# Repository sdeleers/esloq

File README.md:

# esloq
Project date: 2014-2016

Esloq is a startup I worked on from 2014 to 2016. All code written by Kenny Kuchera and me.

Esloq is a door lock that can be opened with a smartphone via Bluetooth. It consists of a wooden box that is mounted on the door lock cylinder. The wooden box contains the printed circuit board and a motor that actuates the lock.

A demo video of the esloq:

Esloq uses authentication and encryption to ensure that only the people you invite can enter. Whenever you want to open a door with your phone, the phone requests a ticket from the esloq webserver. The server returns the ticket that is authenticated encrypted under a symmetric key that is shared between the door lock and the esloq webserver (the phone does not have this key). The phone then forwards this ticket to the lock which verifies its authenticity and opens the door if it's valid.

This repository contains:
- the Kicad design files to make the printed circuit board (folder /pcb/)
- the software running on the microcontroller (folder /firmware/)
- the Android app that connects with the door lock (folder /android/)
- the code running on the webserver (folder /webserver/)

The printed circuit board:

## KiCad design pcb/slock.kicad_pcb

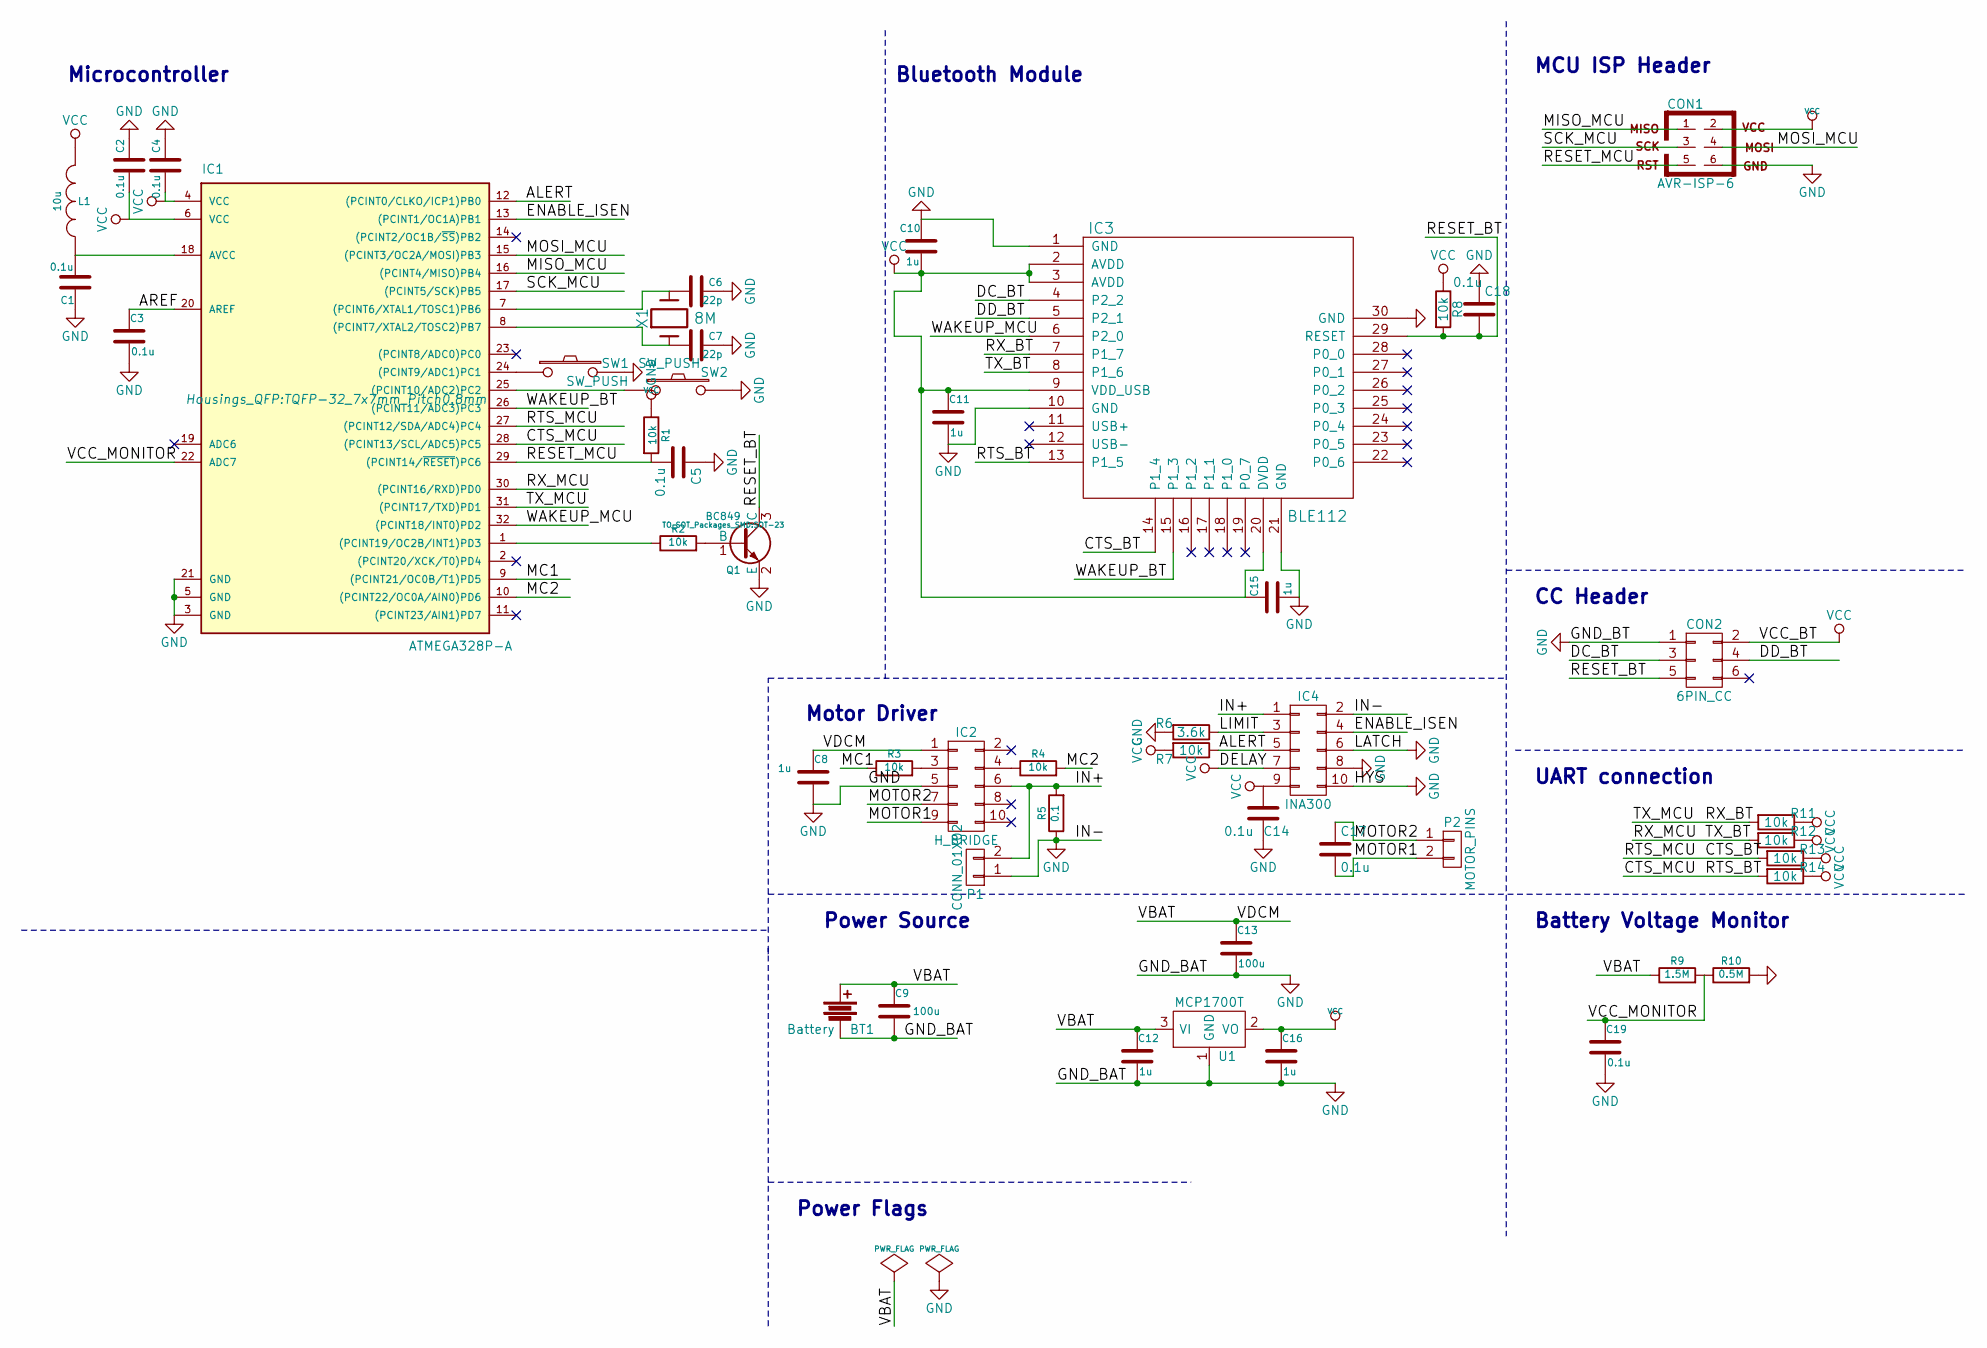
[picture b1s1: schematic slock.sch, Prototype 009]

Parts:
BT1: Battery; Connectors_JST_S2B-PH-SM4-TB
C1, C2, C3, C4, C5, C14, C17, C18, C19: 0.1u; C_0603_HandSoldering
C6, C7: 22p; C_0603_HandSoldering
C8, C10, C11, C12, C15, C16: 1u; C_0603_HandSoldering
C9, C13: 100u; c_elec_6.3x5.8
CON1: AVR-ISP-6; Pin_Header_Straight_2x03
CON2: 6PIN_CC; Pin_Header_Straight_2x03
IC1: ATMEGA328P-A; TQFP-32_7x7mm_Pitch0.8mm
IC2: H_BRIDGE; SOIC-10
IC3: BLE112
IC4: INA300; PWSON10
L1: 10u; C_0603_HandSoldering
P1: CONN_01X02; Pin_Header_Straight_1x02
P2: MOTOR_PINS; Connectors_JST_S2B-PH-SM4-TB
Q1: BC849; SOT-23
R1, R2, R3, R4, R7, R8, R11, R12, R13, R14: 10k; R_0603_HandSoldering
R5: 0.1; R_0603_HandSoldering
R6: 3.6k; R_0603_HandSoldering
R9: 1.5M; R_0603_HandSoldering
R10: 0.5M; R_0603_HandSoldering
SW1, SW2: SW_PUSH; Push_E-Switch_KS01Q01
U1: MCP1700T; SOT-23
X1: 8M; Crystal_AMB3

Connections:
/ALERT: IC1.12 ((PCINT0/CLKO/ICP1)PB0), IC4.5, R7.1
/AREF: C3.1, IC1.20 (AREF)
/CTS_BT: IC1.27 ((PCINT12/SDA/ADC4)PC4), IC3.14 (P1_4), R13.2
/CTS_MCU: IC1.28 ((PCINT13/SCL/ADC5)PC5), IC3.13 (P1_5), R14.2
/DC_BT: CON2.3, IC3.4 (P2_2)
/DD_BT: CON2.4, IC3.5 (P2_1)
/ENABLE_ISEN: IC1.13 ((PCINT1/OC1A)PB1), IC4.4
/IN+: IC2.6, IC4.1, P1.2, R5.2
/LIMIT: IC4.3, R6.1
/MC1: IC1.9 ((PCINT21/OC0B/T1)PD5), R3.1
/MC2: IC1.10 ((PCINT22/OC0A/AIN0)PD6), R4.2
/MISO_MCU: CON1.1, IC1.16 ((PCINT4/MISO)PB4)
/MOSI_MCU: CON1.4, IC1.15 ((PCINT3/OC2A/MOSI)PB3)
/MOTOR1: C17.2, IC2.9, P2.2
/MOTOR2: C17.1, IC2.7, P2.1
/RESET_BT: C18.2, CON2.5, IC3.29 (RESET), Q1.3 (C), R8.2
/RESET_MCU: C5.2, CON1.5, IC1.29 ((PCINT14/~RESET~)PC6), R1.2
/RX_BT: IC1.31 ((PCINT17/TXD)PD1), IC3.7 (P1_7), R11.2
/RX_MCU: IC1.30 ((PCINT16/RXD)PD0), IC3.8 (P1_6), R12.2
/SCK_MCU: CON1.3, IC1.17 ((PCINT5/SCK)PB5)
/VBAT: BT1.1, C8.1, C9.1, C12.1, C13.1, IC2.1, R9.1, U1.3 (VI)
/VCC_MONITOR: C19.1, IC1.22 (ADC7), R9.2, R10.1
/WAKEUP_BT: IC1.26 ((PCINT11/ADC3)PC3), IC3.15 (P1_3)
/WAKEUP_MCU: IC1.32 ((PCINT18/INT0)PD2), IC3.6 (P2_0)
GND: BT1.2, C1.1, C2.2, C3.2, C4.2, C5.1, C6.2, C7.2, C8.2, C9.2, C10.1, C11.2, C12.2, C13.2, C14.1, C15.2, C16.2, C18.1, C19.2, CON1.6, CON2.1, IC1.3 (GND), IC1.5 (GND), IC1.21 (GND), IC2.5, IC3.1 (GND), IC3.10 (GND), IC3.21 (GND), IC3.30 (GND), IC4.2, IC4.6, IC4.8, IC4.10, P1.1, Q1.2 (E), R5.1, R6.2, R10.2, SW1.2, SW2.2, U1.1 (GND)
unnamed: C1.2, IC1.18 (AVCC), L1.1
unnamed: C6.1, IC1.7 ((PCINT6/XTAL1/TOSC1)PB6), X1.2
unnamed: C7.1, IC1.8 ((PCINT7/XTAL2/TOSC2)PB7), X1.1
unnamed: IC1.1 ((PCINT19/OC2B/INT1)PD3), R2.1
unnamed: IC1.24 ((PCINT9/ADC1)PC1), SW1.1
unnamed: IC1.25 ((PCINT10/ADC2)PC2), SW2.1
unnamed: IC2.3, R3.2
unnamed: IC2.4, R4.1
unnamed: Q1.1 (B), R2.2
VCC: C2.1, C4.1, C10.2, C11.1, C14.2, C15.1, C16.1, CON1.2, CON2.2, IC1.4 (VCC), IC1.6 (VCC), IC3.2 (AVDD), IC3.3 (AVDD), IC3.9 (VDD_USB), IC3.20 (DVDD), IC4.7, IC4.9, L1.2, R1.1, R7.2, R8.1, R11.1, R12.1, R13.1, R14.1, U1.2 (VO)

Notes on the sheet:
CC Header
MCU ISP Header
Microcontroller
Bluetooth Module
UART connection
Power Source
Motor Driver
Power Flags
Battery Voltage Monitor

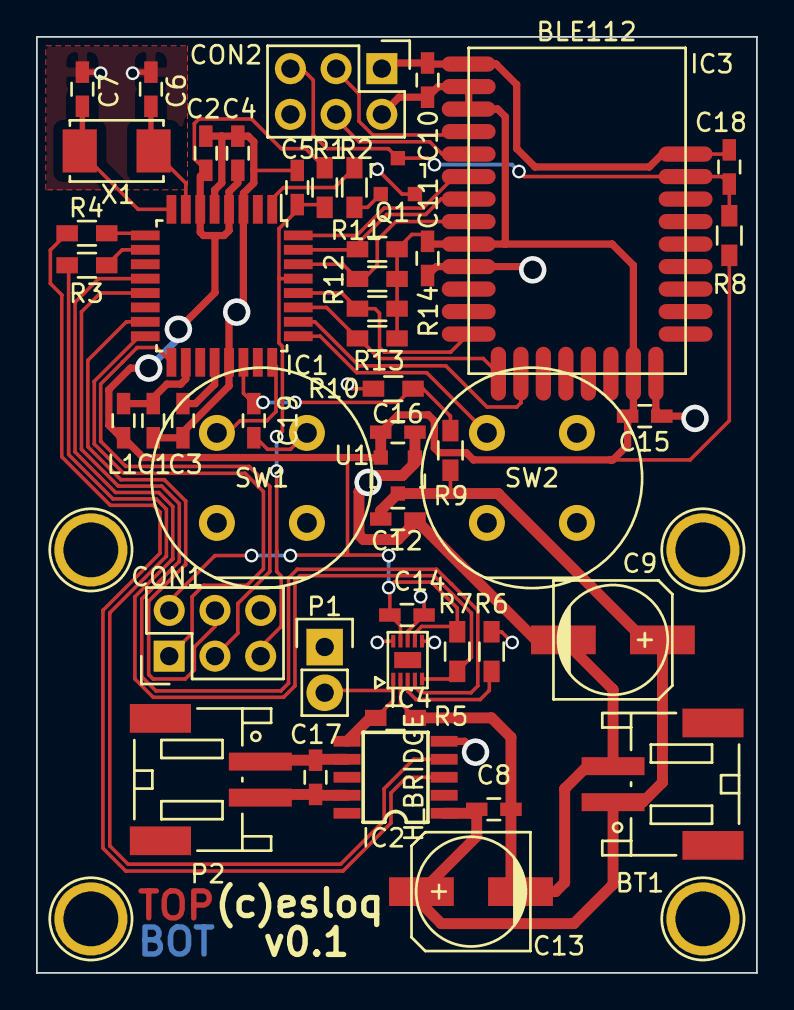
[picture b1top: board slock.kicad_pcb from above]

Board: 2 copper layers, 40.0 x 52.0 mm, 48 parts (0 on the bottom side), 35 nets.

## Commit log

2017-02-26 Add Android app
2017-02-26 Add Printed Circuit Board files.
2017-02-26 Add embedded firmware. Code for microcontroller and Bluetooth chip.
2017-02-26 Add PCB images.
2017-02-26 Add images.
2017-03-28 Add webserver code. Add gitignore file.
